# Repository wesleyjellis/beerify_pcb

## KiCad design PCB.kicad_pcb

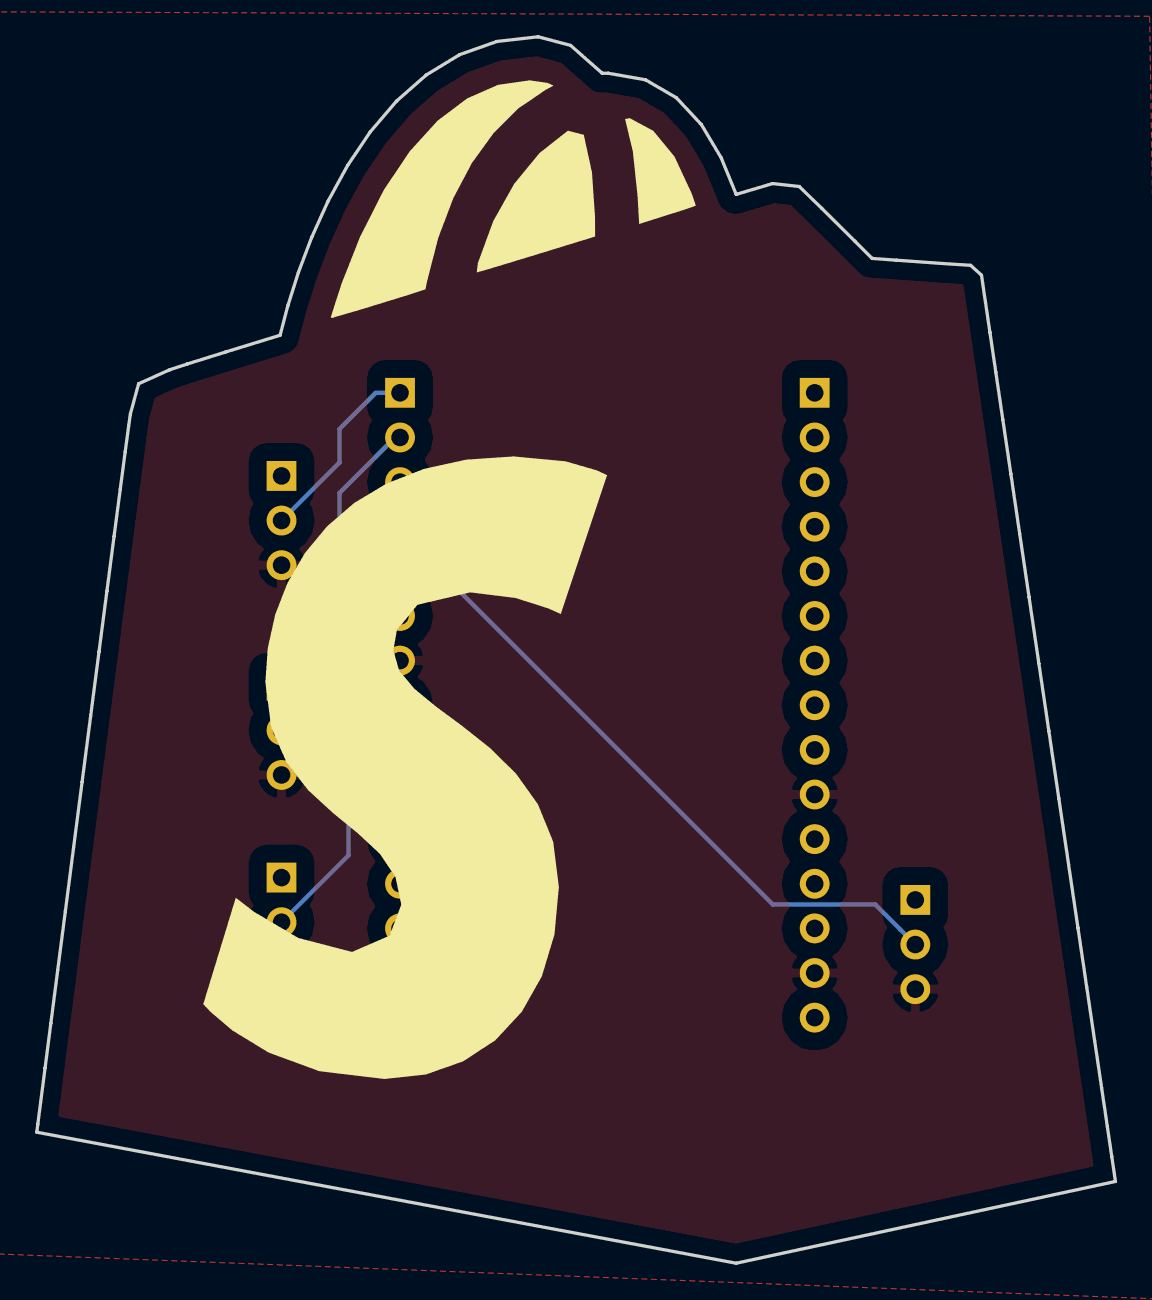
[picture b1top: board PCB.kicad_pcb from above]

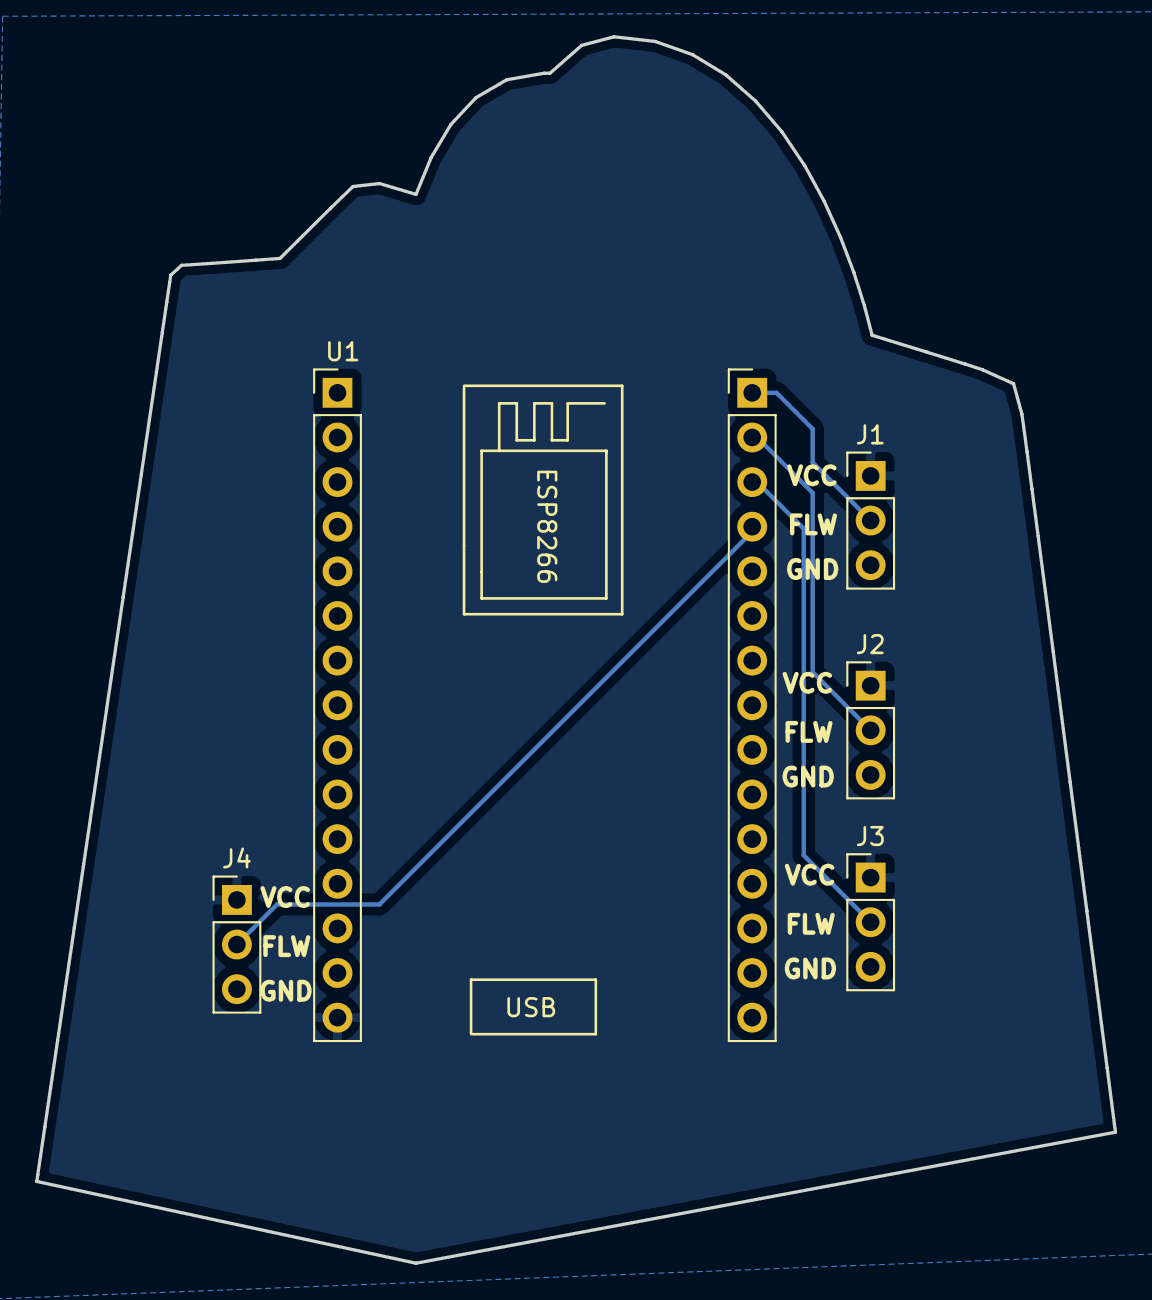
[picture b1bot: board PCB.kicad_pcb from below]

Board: 2 copper layers, 61.4 x 69.8 mm, 6 parts (5 on the bottom side), 6 nets.

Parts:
J1, J2, J3, J4: Conn_01x03_Female; Pin_Header_Straight_1x03_Pitch2.54mm
U1: ESP8266; esp8266
svg2mod: G***; outline

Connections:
/FLOW1: J1.2, U1.16
/FLOW2: J2.2, U1.17
/FLOW3: J3.2, U1.18
/FLOW4: J4.2, U1.19
GND: J1.3, J2.3, J3.3, J4.3, U1.10, U1.14, U1.22, U1.29
VCC: J1.1, J2.1, J3.1, J4.1, U1.15

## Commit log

2018-09-06 All the things (ordered PCB)
